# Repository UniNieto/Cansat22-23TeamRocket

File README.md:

# https://user-images.githubusercontent.com/94926499/228314093-6122f187-c9ed-4645-8bf7-ff298075538c.PNG
lo de arriba es un link a una captura de pantalla con casi todo lo de la quenta
De momento solo tiene una quenta de twitter con la contraseña mongolo99 si no os deja poner la m en mayuscula

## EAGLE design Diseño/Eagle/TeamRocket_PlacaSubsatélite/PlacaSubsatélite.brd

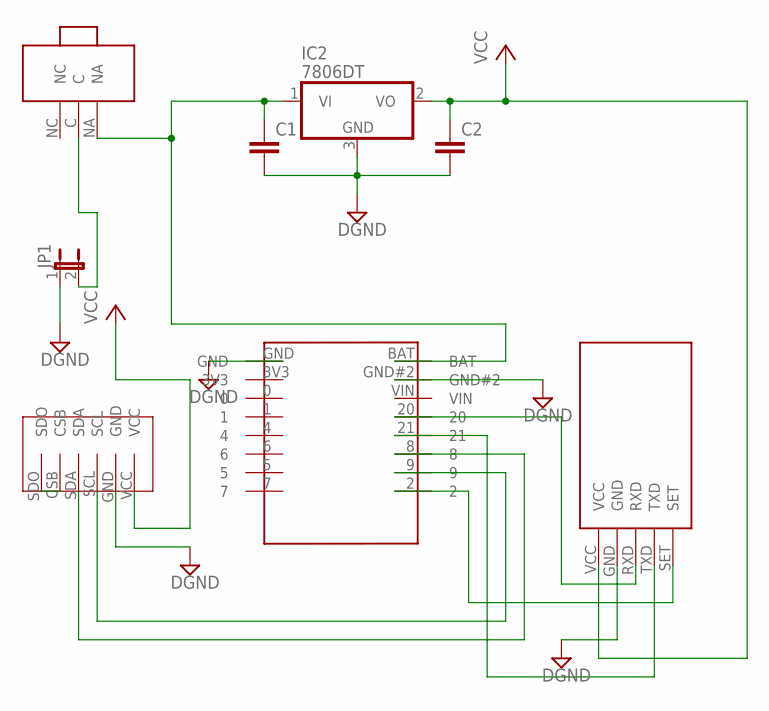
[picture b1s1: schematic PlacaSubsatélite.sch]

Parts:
C1, C2: C-EUC1210; C1210
IC2: 7806DT; TO252
JP1: JP1E; JP1
U$1: BMP280
U$2: MODULO_RADIO; MÓDULO_RADIO
U$3: ESP32
U$4: SWITCH

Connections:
DGND: C1.2, C2.2, IC2.3 (GND), JP1.1, U$1.GND, U$2.GND, U$3.GND, U$3.GND#2
unnamed: C1.1, IC2.1 (VI), U$3.BAT, U$4.NA
unnamed: JP1.2, U$4.C
unnamed: U$1.SDA, U$3.8
unnamed: U$1.SCL, U$3.9
unnamed: U$2.SET, U$3.2
unnamed: U$2.RXD, U$3.20
unnamed: U$2.TXD, U$3.21
unnamed: U$1.CSB, U$1.SDO
VCC: C2.1, IC2.2 (VO), U$1.VCC, U$2.VCC

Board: 2 copper layers, 8 parts (0 on the bottom side), 10 nets, no tracks yet.

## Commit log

2022-11-29 DEPARTAMENTOS
2022-11-29 Webgrafía Baterias
    Primer enlace para baterías de litio
2023-01-19 Create Partes
2023-03-21 Main board updated
2023-03-28 New Paraglider Document
